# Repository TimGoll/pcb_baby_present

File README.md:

# pcb_baby_present
 
https://www.reichelt.de/step-up-adj-0-8--14-v-1-24--14-v-so-8-lm-2623-amm-p187641.html?CCOUNTRY=445&LANGUAGE=de&trstct=pos_0&nbc=1&&r=1
https://lcsc.com/product-detail/Schottky-Barrier-Diodes-SBD_YFW-SS34_C1884574.html
https://lcsc.com/search?q=4.7uH%203A

https://www.electronics-lab.com/project/2-4v-to-5v-step-up-dc-dc-converter/
https://nettigo.eu/products/dc-dc-step-up-converter-hx3242-5v-1-2a-usb-a

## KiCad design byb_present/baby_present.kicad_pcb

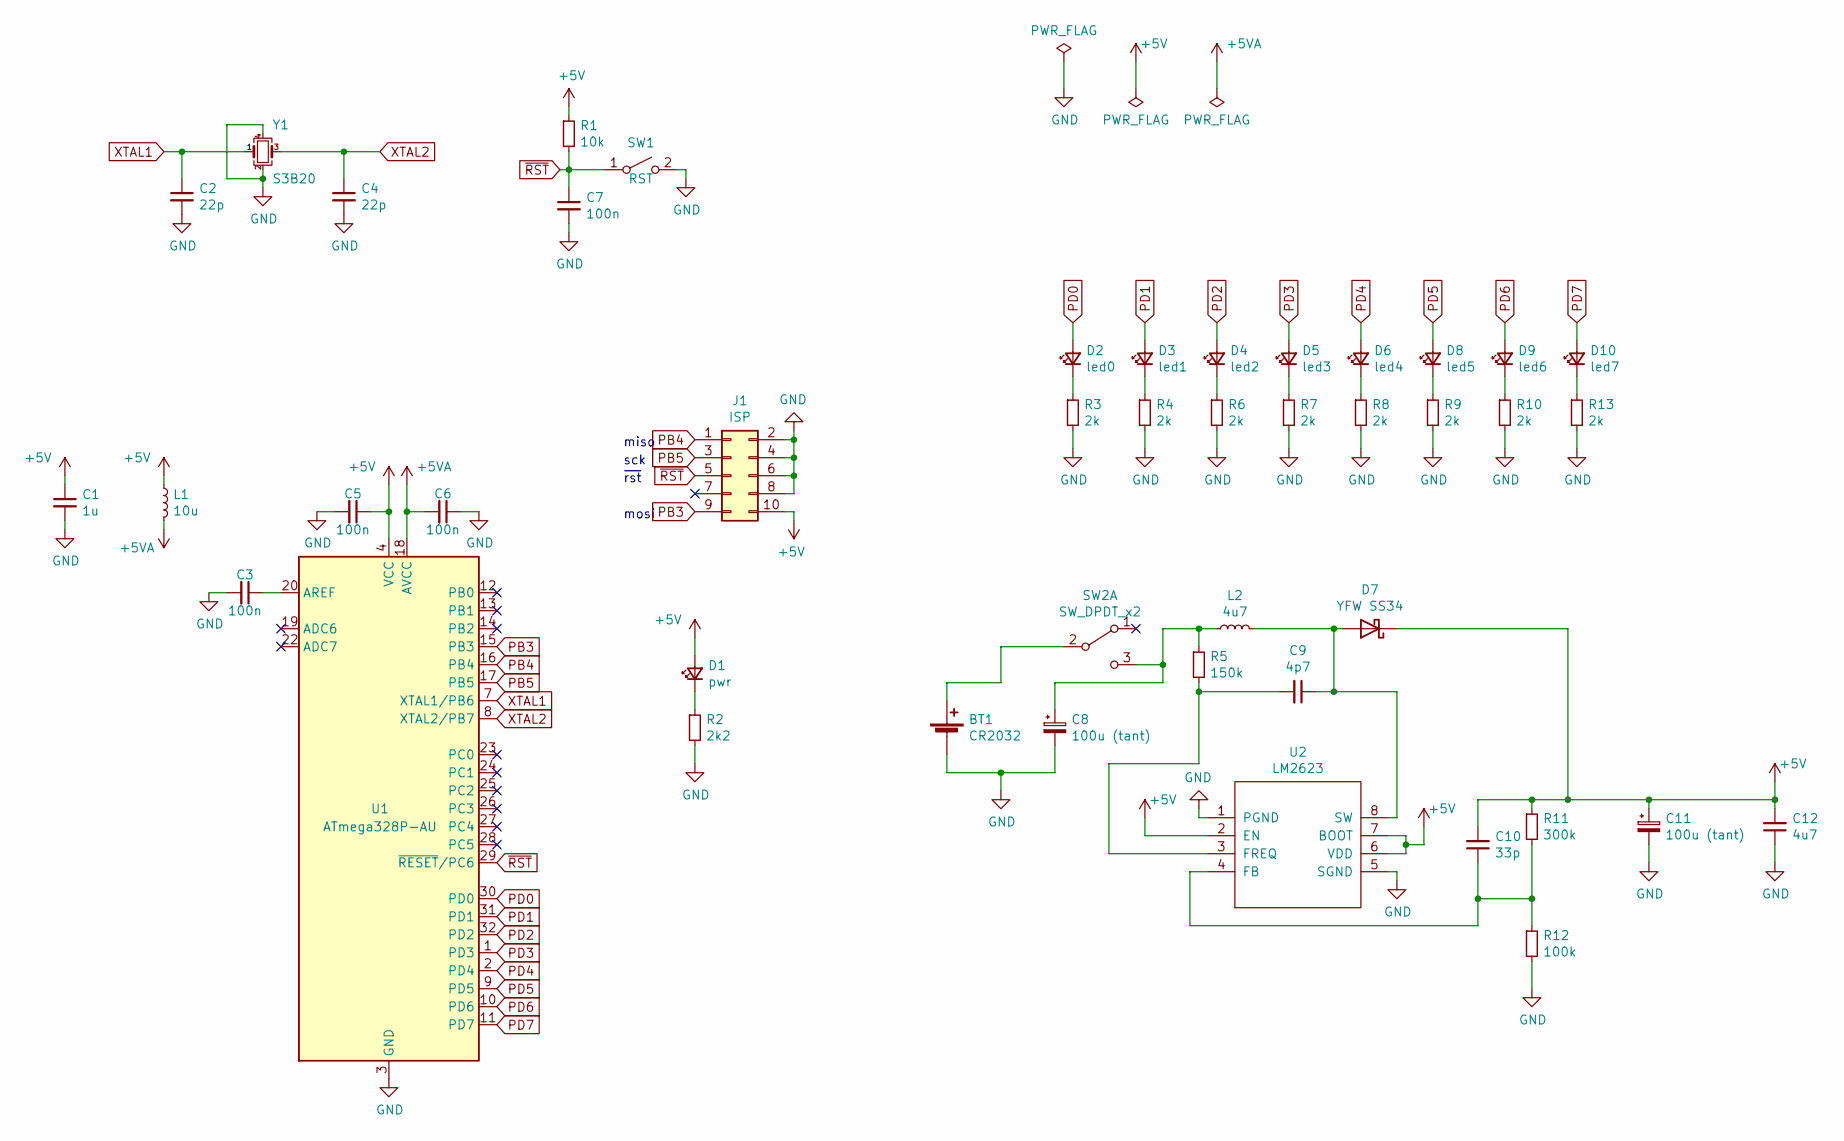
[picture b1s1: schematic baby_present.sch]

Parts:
BT1: CR2032
C1: 1u; C_0805_2012Metric_Pad1.15x1.40mm_HandSolder
C2, C4: 22p; C_0805_2012Metric_Pad1.15x1.40mm_HandSolder
C3, C5, C6, C7: 100n; C_0805_2012Metric_Pad1.15x1.40mm_HandSolder
C8, C11: 100u (tant); CP_EIA-3216-12_Kemet-S_Pad1.58x1.35mm_HandSolder
C9: 4p7; C_0805_2012Metric_Pad1.15x1.40mm_HandSolder
C10: 33p; C_0805_2012Metric_Pad1.15x1.40mm_HandSolder
C12: 4u7; C_0805_2012Metric_Pad1.15x1.40mm_HandSolder
D1: pwr; LED_0805_2012Metric_Castellated
D2: led0; LED_0805_2012Metric_Pad1.15x1.40mm_HandSolder
D3: led1; LED_0805_2012Metric_Pad1.15x1.40mm_HandSolder
D4: led2; LED_0805_2012Metric_Pad1.15x1.40mm_HandSolder
D5: led3; LED_0805_2012Metric_Pad1.15x1.40mm_HandSolder
D6: led4; LED_0805_2012Metric_Pad1.15x1.40mm_HandSolder
D7: YFW SS34; D_SMC_Handsoldering
D8: led5; LED_0805_2012Metric_Pad1.15x1.40mm_HandSolder
D9: led6; LED_0805_2012Metric_Pad1.15x1.40mm_HandSolder
D10: led7; LED_0805_2012Metric_Pad1.15x1.40mm_HandSolder
J1: ISP; PinSocket_2x05_P2.54mm_Vertical
L1: 10u; L_0805_2012Metric_Pad1.15x1.40mm_HandSolder
L2: 4u7; L_Taiyo-Yuden_NR-60xx_HandSoldering
R1: 10k; R_0805_2012Metric_Pad1.15x1.40mm_HandSolder
R2: 2k2; R_0805_2012Metric_Pad1.15x1.40mm_HandSolder
R3, R4, R6, R7, R8, R9, R10, R13: 2k; R_0805_2012Metric_Pad1.15x1.40mm_HandSolder
R5: 150k; R_0805_2012Metric_Pad1.15x1.40mm_HandSolder
R11: 300k; R_0805_2012Metric_Pad1.15x1.40mm_HandSolder
R12: 100k; R_0805_2012Metric_Pad1.15x1.40mm_HandSolder
SW1: RST; SW_Push_1P1T_NO_6x6mm_H9.5mm
SW2: SW_DPDT_x2; switch_sideways
U1: ATmega328P-AU; TQFP-32_7x7mm_P0.8mm
U2: LM2623; VSSOP-8_3.0x3.0mm_P0.65mm
Y1: S3B20; Crystal_SMD_3225-4Pin_3.2x2.5mm_HandSoldering

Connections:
+5V: C1.1, C5.1, C10.2, C11.1, C12.2, D1.2 (A), D7.1 (K), J1.10, L1.1, R1.1, R11.1, U1.4 (VCC), U1.6 (VCC), U2.2 (EN), U2.6 (VDD), U2.7 (BOOT)
+5VA: C6.2, L1.2, U1.18 (AVCC)
GND: BT1.2 (-), C1.2, C2.2, C3.2, C4.2, C5.2, C6.1, C7.2, C8.2, C11.2, C12.1, J1.2, J1.4, J1.6, J1.8, R2.2, R3.2, R4.2, R6.2, R7.2, R8.2, R9.2, R10.2, R12.2, R13.2, SW1.2 (B), U1.3 (GND), U1.5 (GND), U1.21 (GND), U2.1 (PGND), U2.5 (SGND), Y1.2, Y1.4
unnamed: BT1.1 (+), SW2.2 (B)
unnamed: C3.1, U1.20 (AREF)
unnamed: C8.1, L2.1, R5.1, SW2.3 (C)
unnamed: C9.1, D7.2 (A), L2.2, U2.8 (SW)
unnamed: C9.2, R5.2, U2.3 (FREQ)
unnamed: C10.1, R11.2, R12.1, U2.4 (FB)
unnamed: D1.1 (K), R2.1
unnamed: D2.1 (K), R3.1
unnamed: D3.1 (K), R4.1
unnamed: D4.1 (K), R6.1
unnamed: D5.1 (K), R7.1
unnamed: D6.1 (K), R8.1
unnamed: D8.1 (K), R9.1
unnamed: D9.1 (K), R10.1
unnamed: D10.1 (K), R13.1
PB3: J1.9, U1.15 (PB3)
PB4: J1.1, U1.16 (PB4)
PB5: J1.3, U1.17 (PB5)
PD0: D2.2 (A), U1.30 (PD0)
PD1: D3.2 (A), U1.31 (PD1)
PD2: D4.2 (A), U1.32 (PD2)
PD3: D5.2 (A), U1.1 (PD3)
PD4: D6.2 (A), U1.2 (PD4)
PD5: D8.2 (A), U1.9 (PD5)
PD6: D9.2 (A), U1.10 (PD6)
PD7: D10.2 (A), U1.11 (PD7)
XTAL1: C2.1, U1.7 (XTAL1/PB6), Y1.1
XTAL2: C4.1, U1.8 (XTAL2/PB7), Y1.3
~RST: C7.1, J1.5, R1.2, SW1.1 (A), U1.29 (~RESET~/PC6)

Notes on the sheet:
miso
sck
~rst
mosi

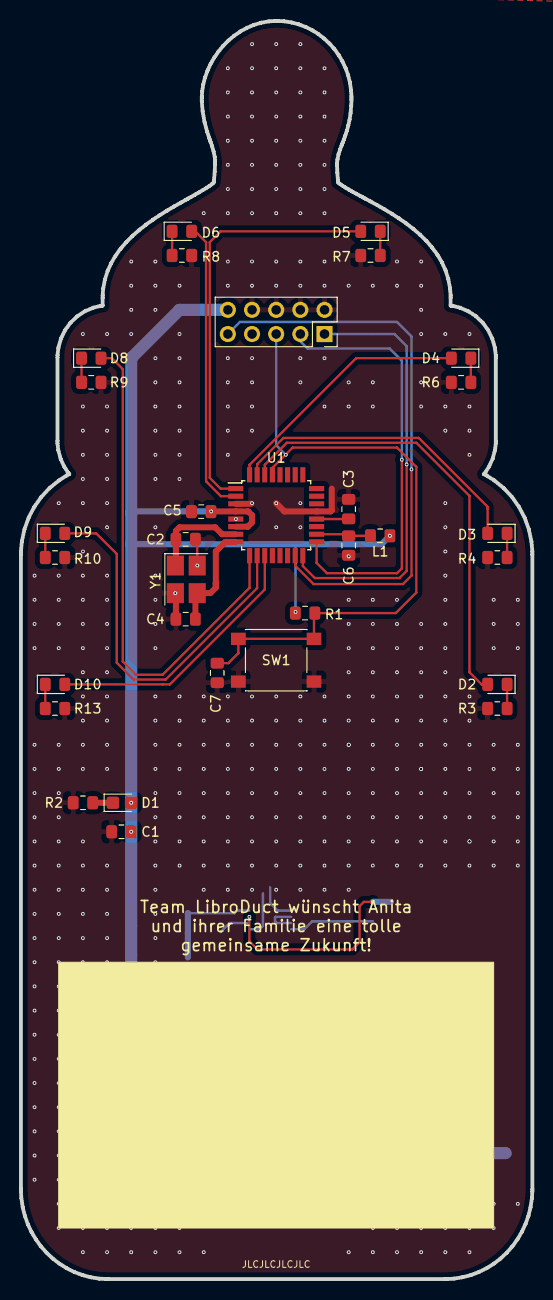
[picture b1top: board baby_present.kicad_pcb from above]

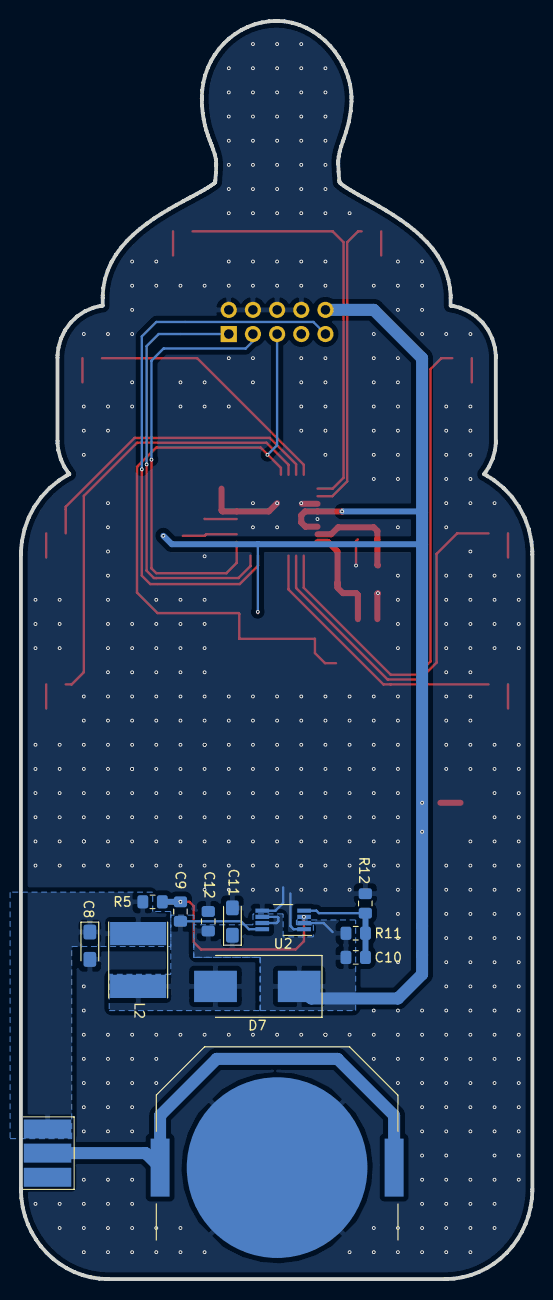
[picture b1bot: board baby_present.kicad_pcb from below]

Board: 2 copper layers, 53.8 x 132.3 mm, 44 parts (13 on the bottom side), 32 nets.

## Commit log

2022-01-03 pcb finished
